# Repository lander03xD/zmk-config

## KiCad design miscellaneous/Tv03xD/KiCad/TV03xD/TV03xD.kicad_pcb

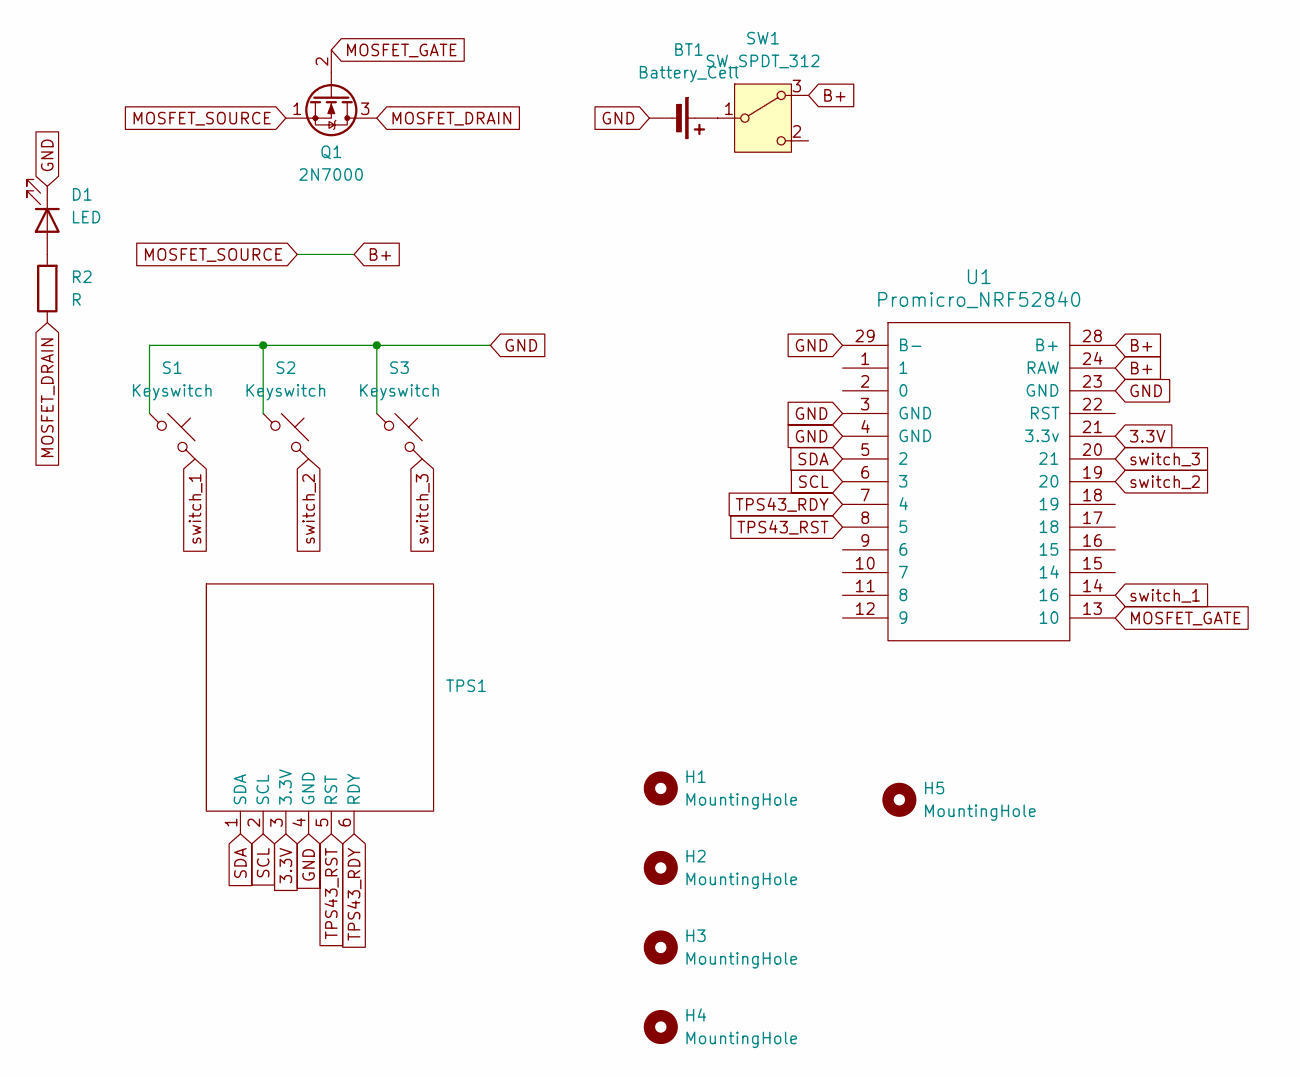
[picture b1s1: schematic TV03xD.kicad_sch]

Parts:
BT1: Battery_Cell; Battery pins
D1: LED; LED_D5.0mm
H1, H2, H3, H4, H5: MountingHole; MountingHole_2.2mm_M2
Q1: 2N7000; TO-92_Inline
R2: R; R_Axial_DIN0207_L6.3mm_D2.5mm_P7.62mm_Horizontal
S1, S2, S3: Keyswitch; Hotswap_Choc_V1V2_1.00u_18.5_throughole
SW1: SW_SPDT_312; powerswitch_SK12D07VG
TPS1: Azoteq ProxSense TPS43
U1: Promicro_NRF52840; Promicro_nrf52840_unprinted

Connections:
3.3V: TPS1.3 (3.3V), U1.21 (3.3v)
B+: Q1.1 (S), SW1.3 (A), U1.24 (RAW), U1.28 (B+)
GND: BT1.2 (-), D1.1 (K), S1.1, S2.1, S3.1, TPS1.4 (GND), U1.3 (GND), U1.4 (GND), U1.23 (GND), U1.29 (B-)
MOSFET_DRAIN: Q1.3 (D), R2.1
MOSFET_GATE: Q1.2 (G), U1.13 (10)
unnamed: BT1.1 (+), SW1.1 (B)
unnamed: D1.2 (A), R2.2
SCL: TPS1.2 (SCL), U1.6 (3)
SDA: TPS1.1 (SDA), U1.5 (2)
TPS43_RDY: TPS1.6 (RDY), U1.7 (4)
TPS43_RST: TPS1.5 (RST), U1.8 (5)
switch_1: S1.2, U1.14 (16)
switch_2: S2.2, U1.19 (20)
switch_3: S3.2, U1.20 (21)

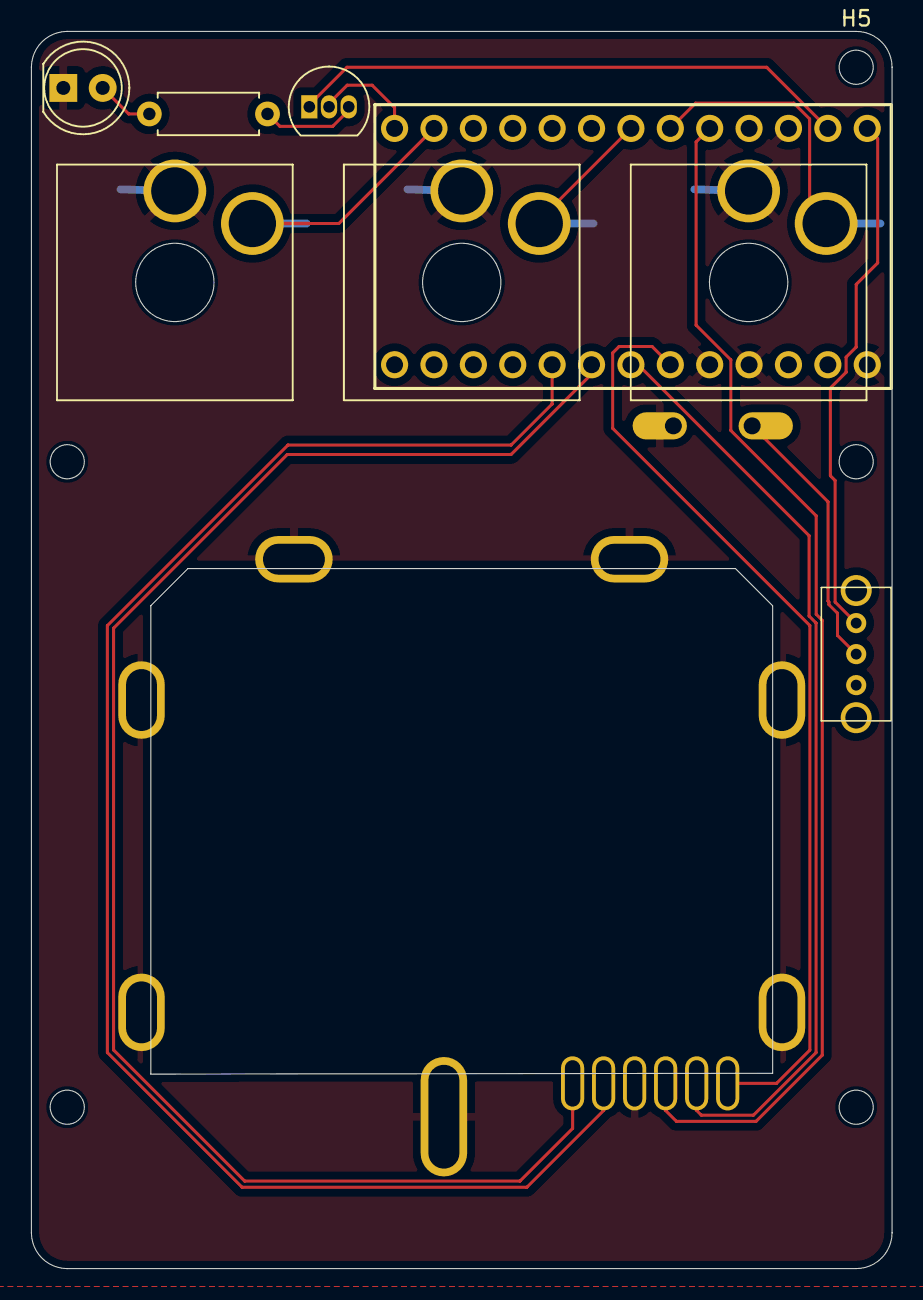
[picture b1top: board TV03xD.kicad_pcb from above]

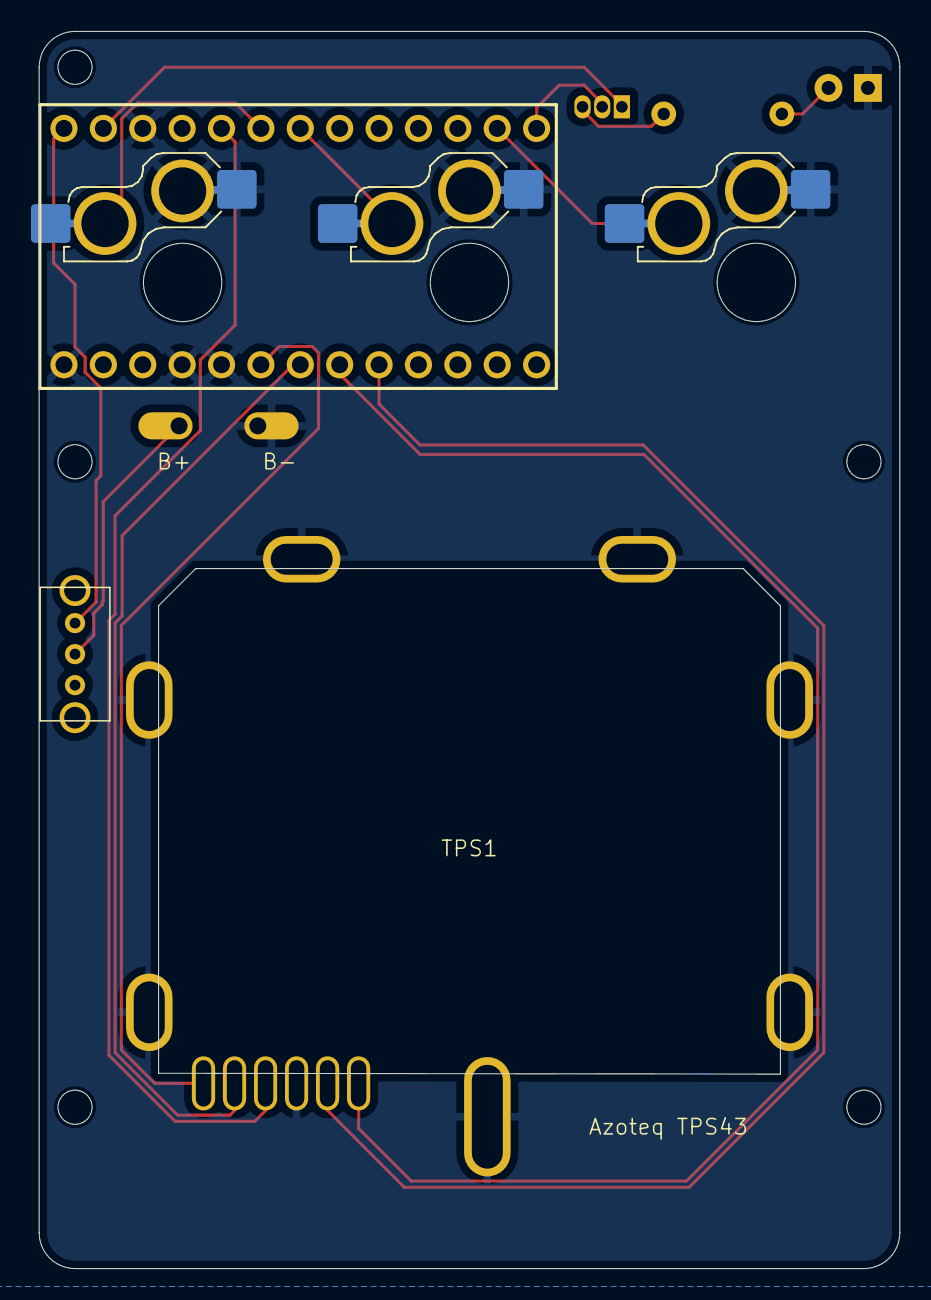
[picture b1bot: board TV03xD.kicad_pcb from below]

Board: 2 copper layers, 55.5 x 79.8 mm, 15 parts (2 on the bottom side), 14 nets.

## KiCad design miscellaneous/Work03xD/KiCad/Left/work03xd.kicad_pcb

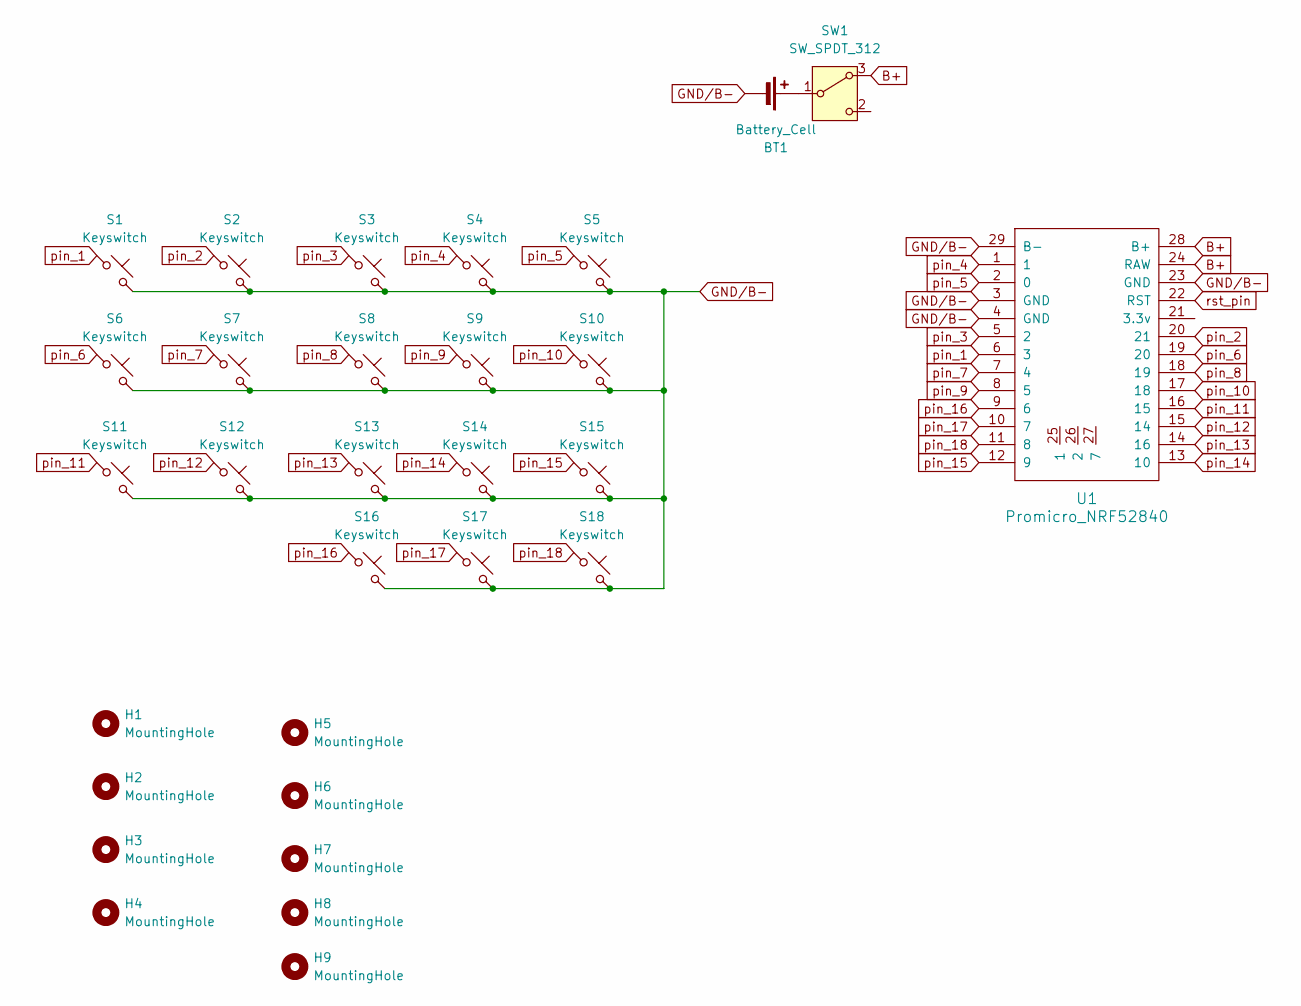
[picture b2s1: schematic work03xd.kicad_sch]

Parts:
BT1: Battery_Cell; Battery pins
H1, H2, H3, H4, H5, H6, H7, H8, H9: MountingHole; MountingHole_2.2mm_M2
S1, S2, S3, S4, S5, S6, S7, S8, S9, S10, S11, S12, S13, S14, S15, S16, S17, S18: Keyswitch; Hotswap_Choc_V1V2_1.00u_18.5_throughole
SW1: SW_SPDT_312; powerswitch_SK12D07VG
U1: Promicro_NRF52840; Promicro_nrf52840_unprinted

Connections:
B+: SW1.3 (A), U1.24 (RAW), U1.28 (B+)
GND/B-: BT1.2 (-), S1.2, S2.2, S3.2, S4.2, S5.2, S6.2, S7.2, S8.2, S9.2, S10.2, S11.2, S12.2, S13.2, S14.2, S15.2, S16.2, S17.2, S18.2, U1.3 (GND), U1.4 (GND), U1.23 (GND), U1.29 (B-)
unnamed: BT1.1 (+), SW1.1 (B)
pin_1: S1.1, U1.6 (3)
pin_2: S2.1, U1.20 (21)
pin_3: S3.1, U1.5 (2)
pin_4: S4.1, U1.1
pin_5: S5.1, U1.2 (0)
pin_6: S6.1, U1.19 (20)
pin_7: S7.1, U1.7 (4)
pin_8: S8.1, U1.18 (19)
pin_9: S9.1, U1.8 (5)
pin_10: S10.1, U1.17 (18)
pin_11: S11.1, U1.16 (15)
pin_12: S12.1, U1.15 (14)
pin_13: S13.1, U1.14 (16)
pin_14: S14.1, U1.13 (10)
pin_15: S15.1, U1.12 (9)
pin_16: S16.1, U1.9 (6)
pin_17: S17.1, U1.10 (7)
pin_18: S18.1, U1.11 (8)
rst_pin: U1.22 (RST)

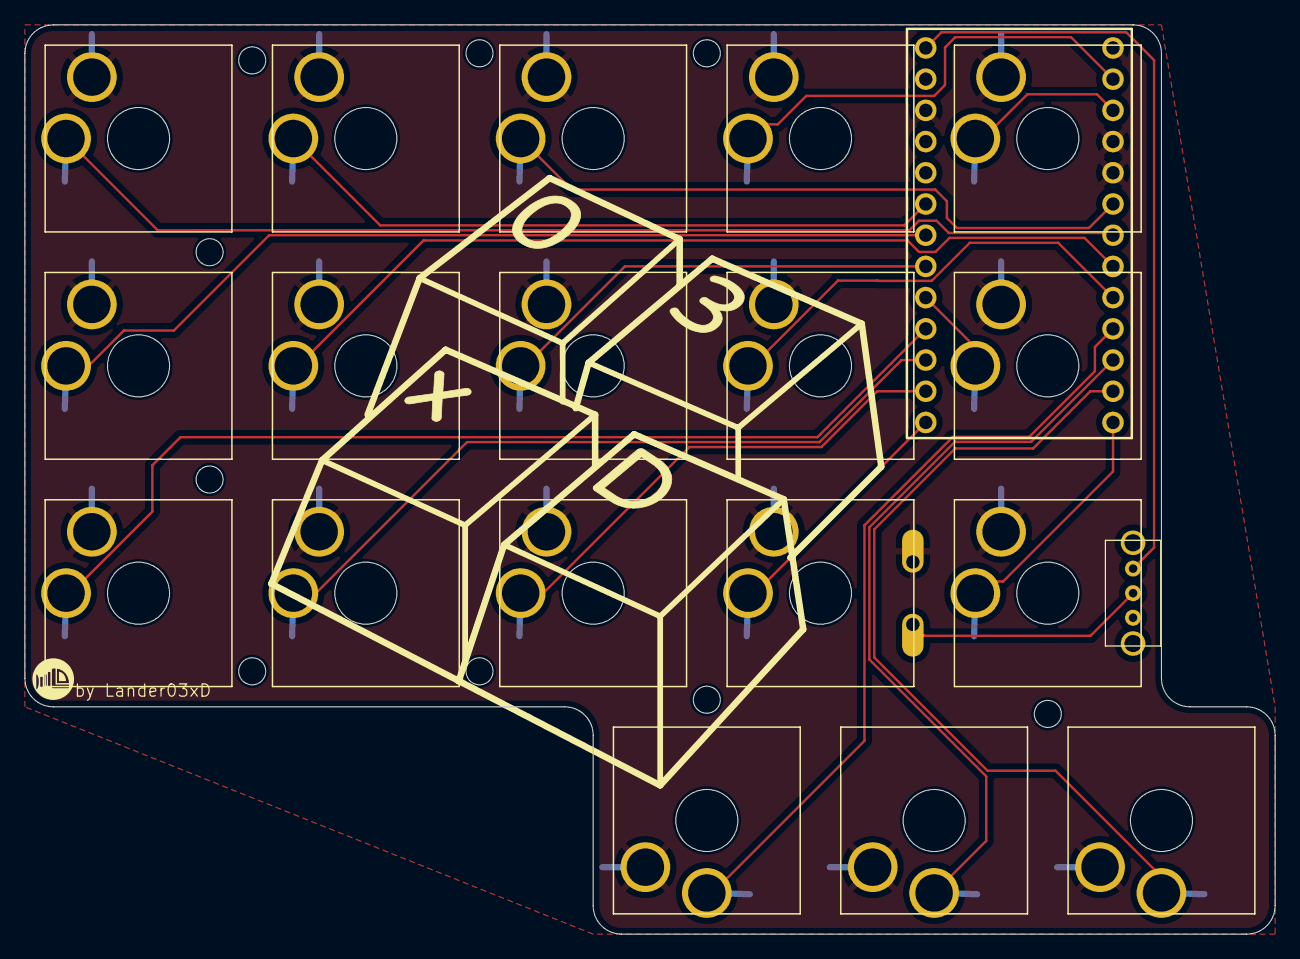
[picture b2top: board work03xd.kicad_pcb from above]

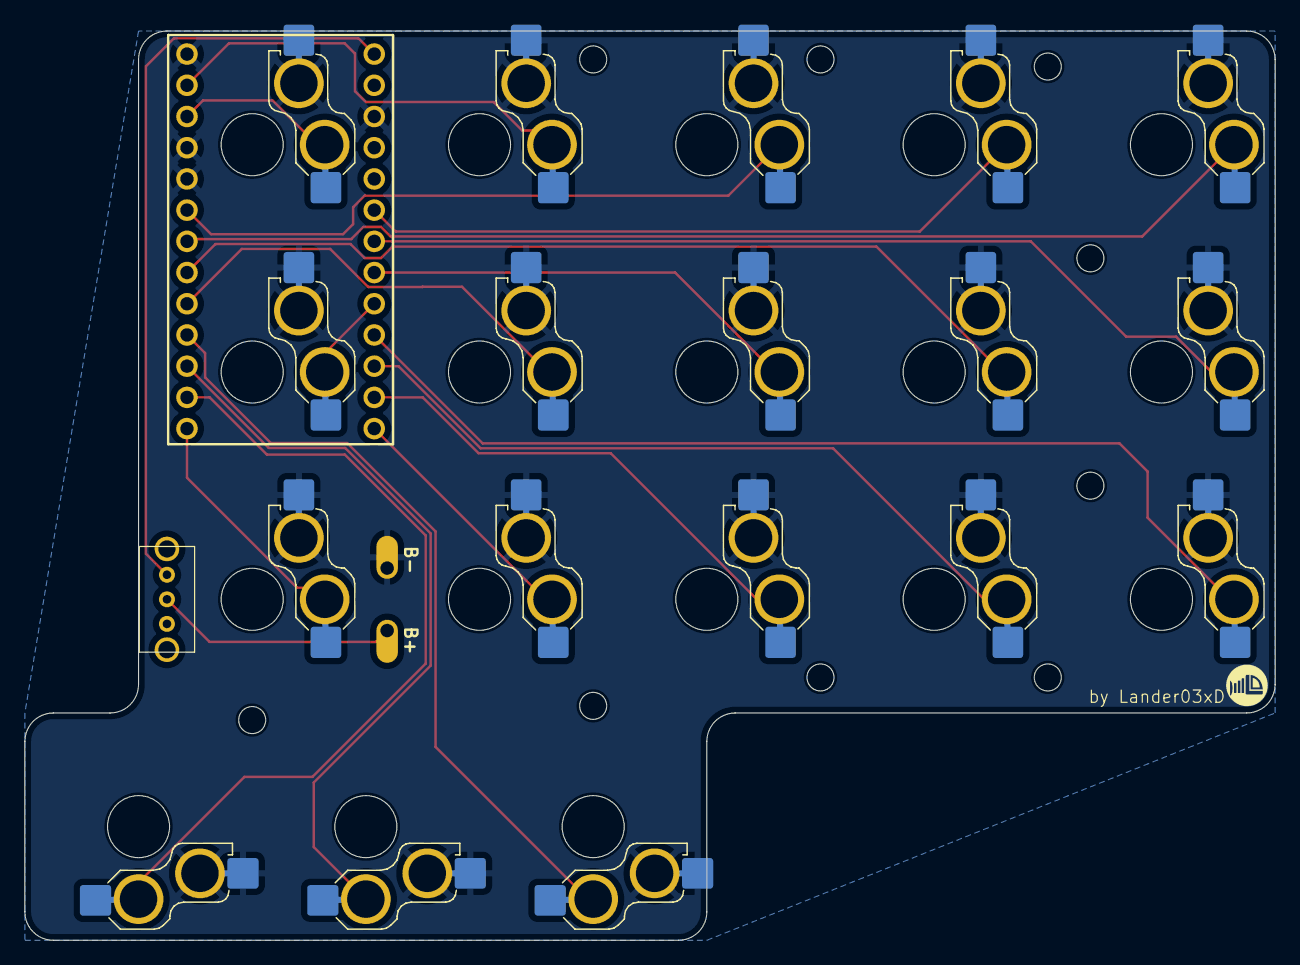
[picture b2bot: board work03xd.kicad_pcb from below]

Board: 2 copper layers, 101.8 x 74.0 mm, 30 parts (2 on the bottom side), 21 nets.

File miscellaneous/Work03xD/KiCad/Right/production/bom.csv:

Designator,Footprint,Quantity,Value,LCSC Part #
BT1,Battery pins,1,Battery_Cell,
"S1, S10, S11, S12, S13, S14, S15, S16, S17, S18, S2, S3, S4, S5, S6, S7, S8, S9",Hotswap_Choc_V1V2_1.00u_18.5_throughole,18,Keyswitch,
SW1,powerswitch_SK12D07VG,1,SW_SPDT_312,
U1,Promicro_nrf52840_unprinted,1,Promicro_NRF52840,

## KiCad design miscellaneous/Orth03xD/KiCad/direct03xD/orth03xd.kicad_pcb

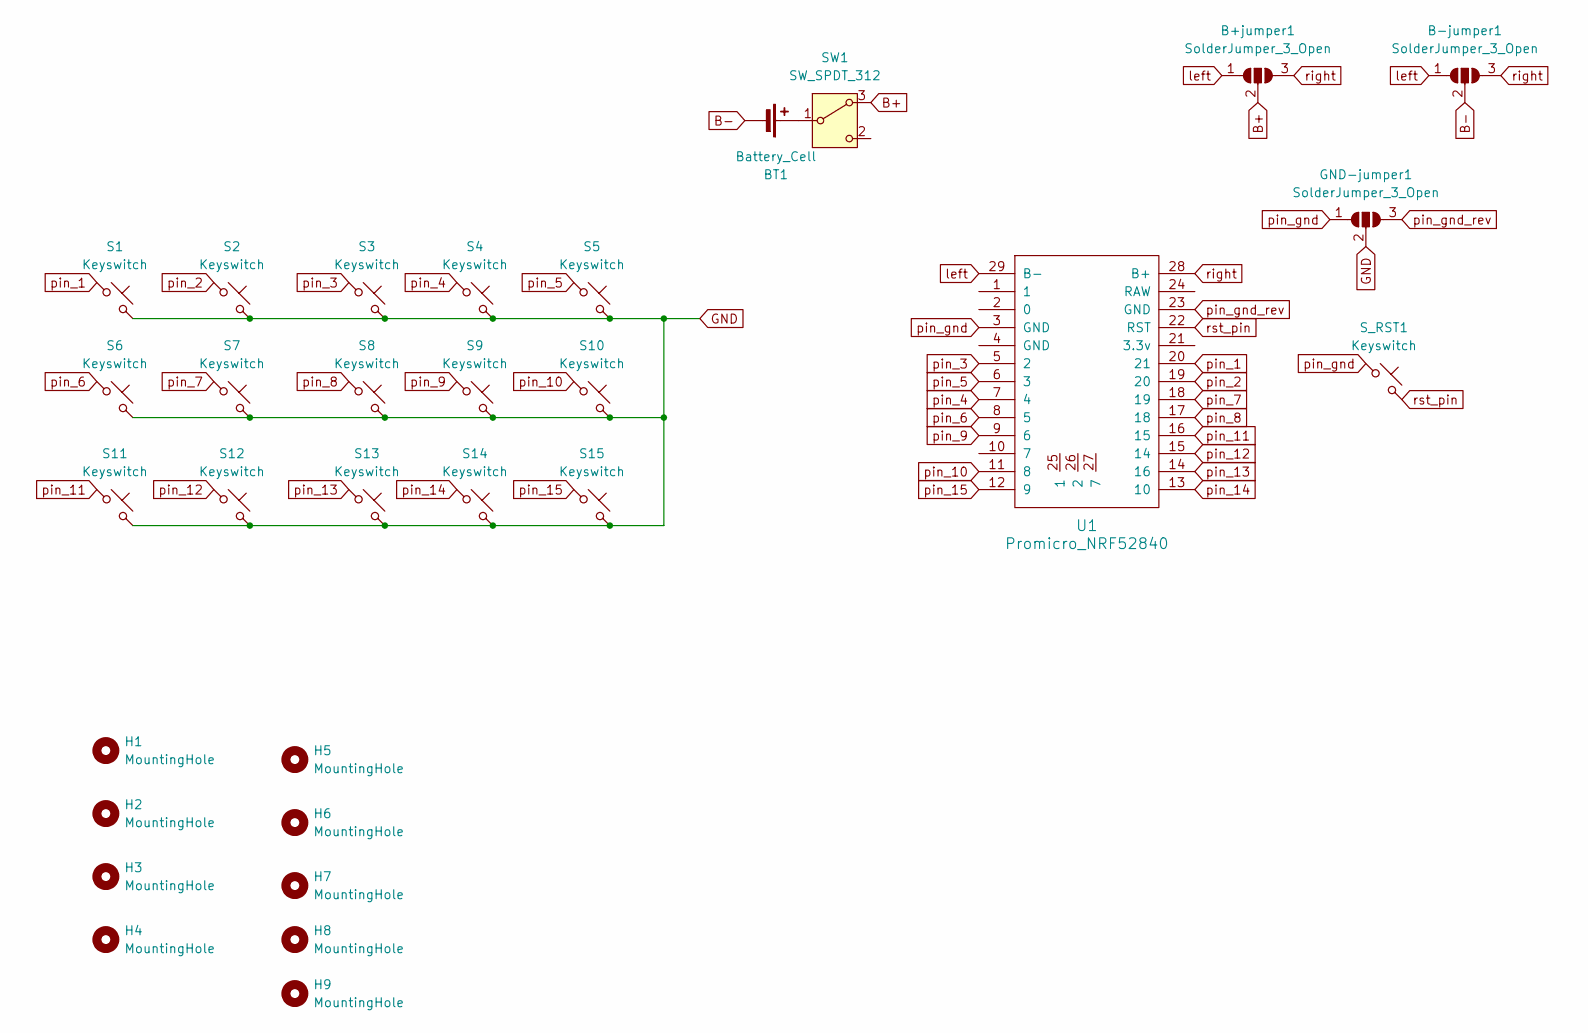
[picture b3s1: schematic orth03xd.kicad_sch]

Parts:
B+jumper1: SolderJumper_3_Open; jumper
B-jumper1: SolderJumper_3_Open; jumper
BT1: Battery_Cell; Battery pins
GND-jumper1: SolderJumper_3_Open; jumper
H1, H2, H3, H4, H5, H6, H7, H8, H9: MountingHole; MountingHole_2.2mm_M2
S1, S2, S3, S4, S5, S6, S7, S8, S9, S10, S11, S12, S13, S14, S15: Keyswitch; Hotswap_MX_1.00u_reversible_18.5mm
SW1: SW_SPDT_312; powerswitch_SK12D07VG
S_RST1: Keyswitch; KAILH_4.3mm_6.2x6.2_switch
U1: Promicro_NRF52840; Promicro_nrf52840_unprinted

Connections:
B+: B+jumper1.2 (C), SW1.3 (A)
B-: B-jumper1.2 (C), BT1.2 (-)
GND: GND-jumper1.2 (C), S1.2, S2.2, S3.2, S4.2, S5.2, S6.2, S7.2, S8.2, S9.2, S10.2, S11.2, S12.2, S13.2, S14.2, S15.2
unnamed: BT1.1 (+), SW1.1 (B)
left: B+jumper1.1 (A), B-jumper1.1 (A), U1.29 (B-)
pin_1: S1.1, U1.20 (21)
pin_2: S2.1, U1.19 (20)
pin_3: S3.1, U1.5 (2)
pin_4: S4.1, U1.7 (4)
pin_5: S5.1, U1.6 (3)
pin_6: S6.1, U1.8 (5)
pin_7: S7.1, U1.18 (19)
pin_8: S8.1, U1.17 (18)
pin_9: S9.1, U1.9 (6)
pin_10: S10.1, U1.11 (8)
pin_11: S11.1, U1.16 (15)
pin_12: S12.1, U1.15 (14)
pin_13: S13.1, U1.14 (16)
pin_14: S14.1, U1.13 (10)
pin_15: S15.1, U1.12 (9)
pin_gnd: GND-jumper1.1 (A), S_RST1.1, U1.3 (GND)
pin_gnd_rev: GND-jumper1.3 (B), U1.23 (GND)
right: B+jumper1.3 (B), B-jumper1.3 (B), U1.28 (B+)
rst_pin: S_RST1.2, U1.22 (RST)

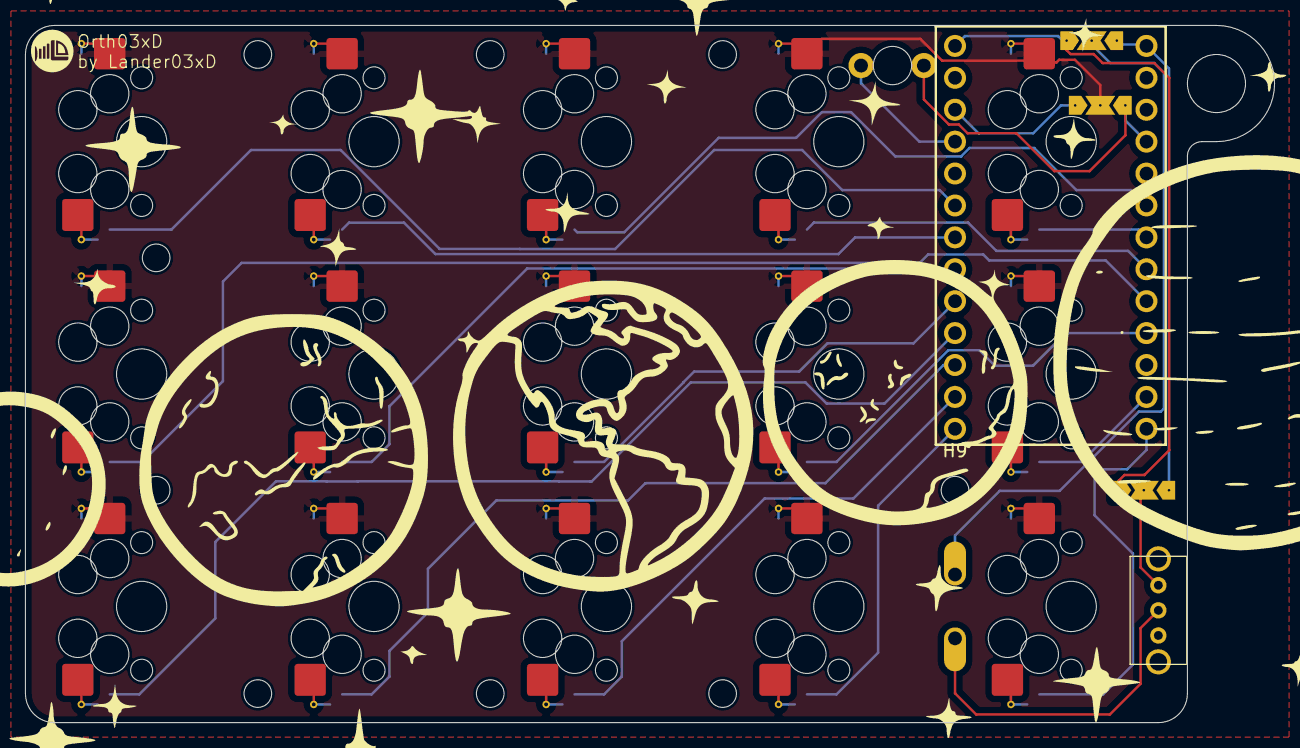
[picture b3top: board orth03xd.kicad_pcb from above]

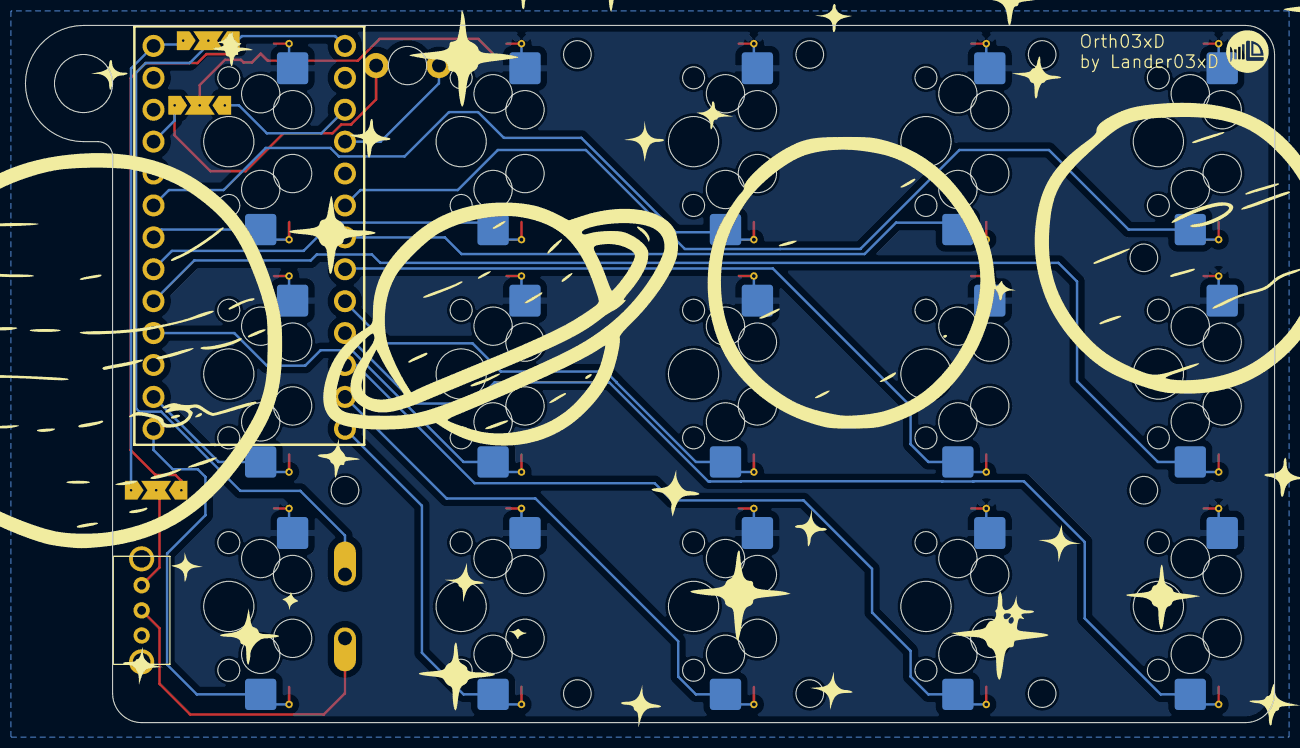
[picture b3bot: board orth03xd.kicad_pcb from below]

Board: 2 copper layers, 99.4 x 55.5 mm, 31 parts (4 on the bottom side), 24 nets.

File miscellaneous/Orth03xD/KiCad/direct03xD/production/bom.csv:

Designator,Footprint,Quantity,Value,LCSC Part #
BT1,Battery pins,1,Battery_Cell,
"S1, S10, S11, S12, S13, S14, S15, S2, S3, S4, S5, S6, S7, S8, S9",Hotswap_MX_1.00u_reversible_18.5mm,15,Keyswitch,
SW1,powerswitch_SK12D07VG,1,SW_SPDT_312,
S_RST1,KAILH_4.3mm_6.2x6.2_switch,1,Keyswitch,
U1,Promicro_nrf52840_unprinted,1,Promicro_NRF52840,

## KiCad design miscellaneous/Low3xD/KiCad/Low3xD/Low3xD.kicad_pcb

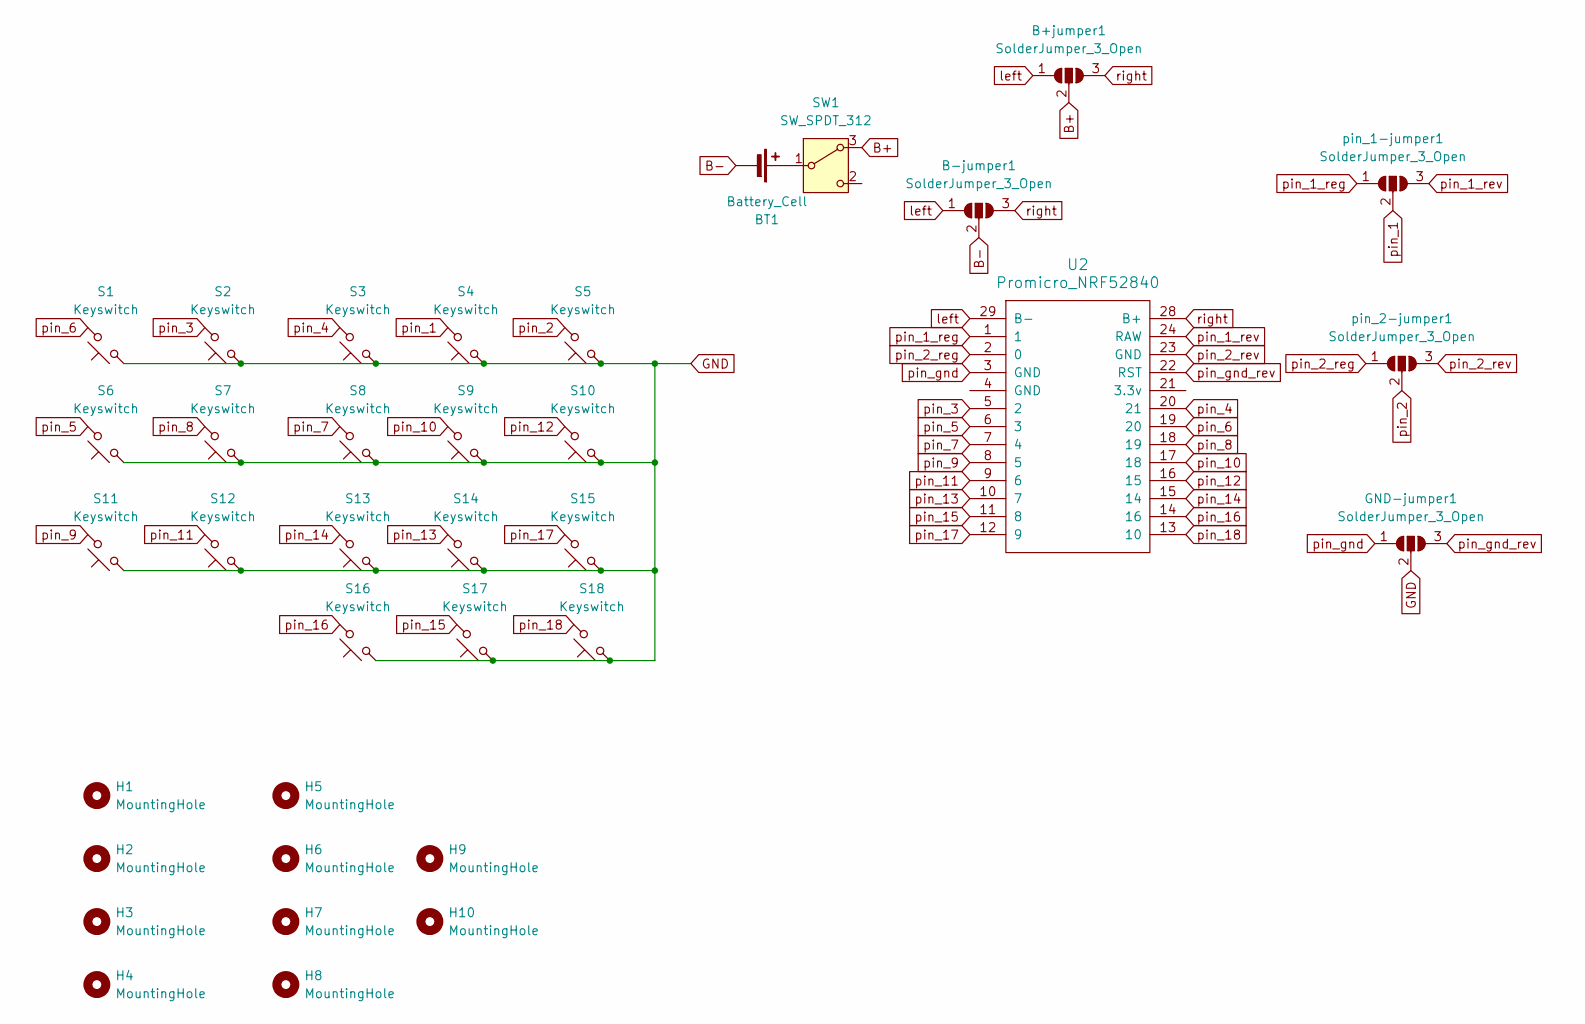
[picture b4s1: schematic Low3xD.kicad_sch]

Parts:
B+jumper1: SolderJumper_3_Open; jumper
B-jumper1: SolderJumper_3_Open; jumper
BT1: Battery_Cell; Battery pins
GND-jumper1: SolderJumper_3_Open; jumper
H1, H2, H3, H4, H5, H6, H7, H8, H9, H10: MountingHole; MountingHole_2.2mm_M2
S1, S2, S3, S4, S5, S6, S7, S8, S9, S10, S11, S12, S13, S14, S15, S16, S17, S18: Keyswitch; Hotswap_Choc_V1V2_rev_1.00u
SW1: SW_SPDT_312; SS-01B 1.5mm
U2: Promicro_NRF52840; Promicro_nrf52840_unprinted
pin_1-jumper1, pin_2-jumper1: SolderJumper_3_Open; jumper

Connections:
B+: B+jumper1.2 (C), SW1.3 (A)
B-: B-jumper1.2 (C), BT1.2 (-)
GND: GND-jumper1.2 (C), S1.1, S2.1, S3.1, S4.1, S5.1, S6.1, S7.1, S8.1, S9.1, S10.1, S11.1, S12.1, S13.1, S14.1, S15.1, S16.1, S17.1, S18.1
unnamed: BT1.1 (+), SW1.1 (B)
left: B+jumper1.1 (A), B-jumper1.1 (A), U2.29 (B-)
pin_1: S4.2, pin_1-jumper1.2 (C)
pin_1_reg: U2.1, pin_1-jumper1.1 (A)
pin_1_rev: U2.24 (RAW), pin_1-jumper1.3 (B)
pin_2: S5.2, pin_2-jumper1.2 (C)
pin_2_reg: U2.2 (0), pin_2-jumper1.1 (A)
pin_2_rev: U2.23 (GND), pin_2-jumper1.3 (B)
pin_3: S2.2, U2.5 (2)
pin_4: S3.2, U2.20 (21)
pin_5: S6.2, U2.6 (3)
pin_6: S1.2, U2.19 (20)
pin_7: S8.2, U2.7 (4)
pin_8: S7.2, U2.18 (19)
pin_9: S11.2, U2.8 (5)
pin_10: S9.2, U2.17 (18)
pin_11: S12.2, U2.9 (6)
pin_12: S10.2, U2.16 (15)
pin_13: S14.2, U2.10 (7)
pin_14: S13.2, U2.15 (14)
pin_15: S17.2, U2.11 (8)
pin_16: S16.2, U2.14 (16)
pin_17: S15.2, U2.12 (9)
pin_18: S18.2, U2.13 (10)
pin_gnd: GND-jumper1.1 (A), U2.3 (GND)
pin_gnd_rev: GND-jumper1.3 (B), U2.22 (RST)
right: B+jumper1.3 (B), B-jumper1.3 (B), U2.28 (B+)

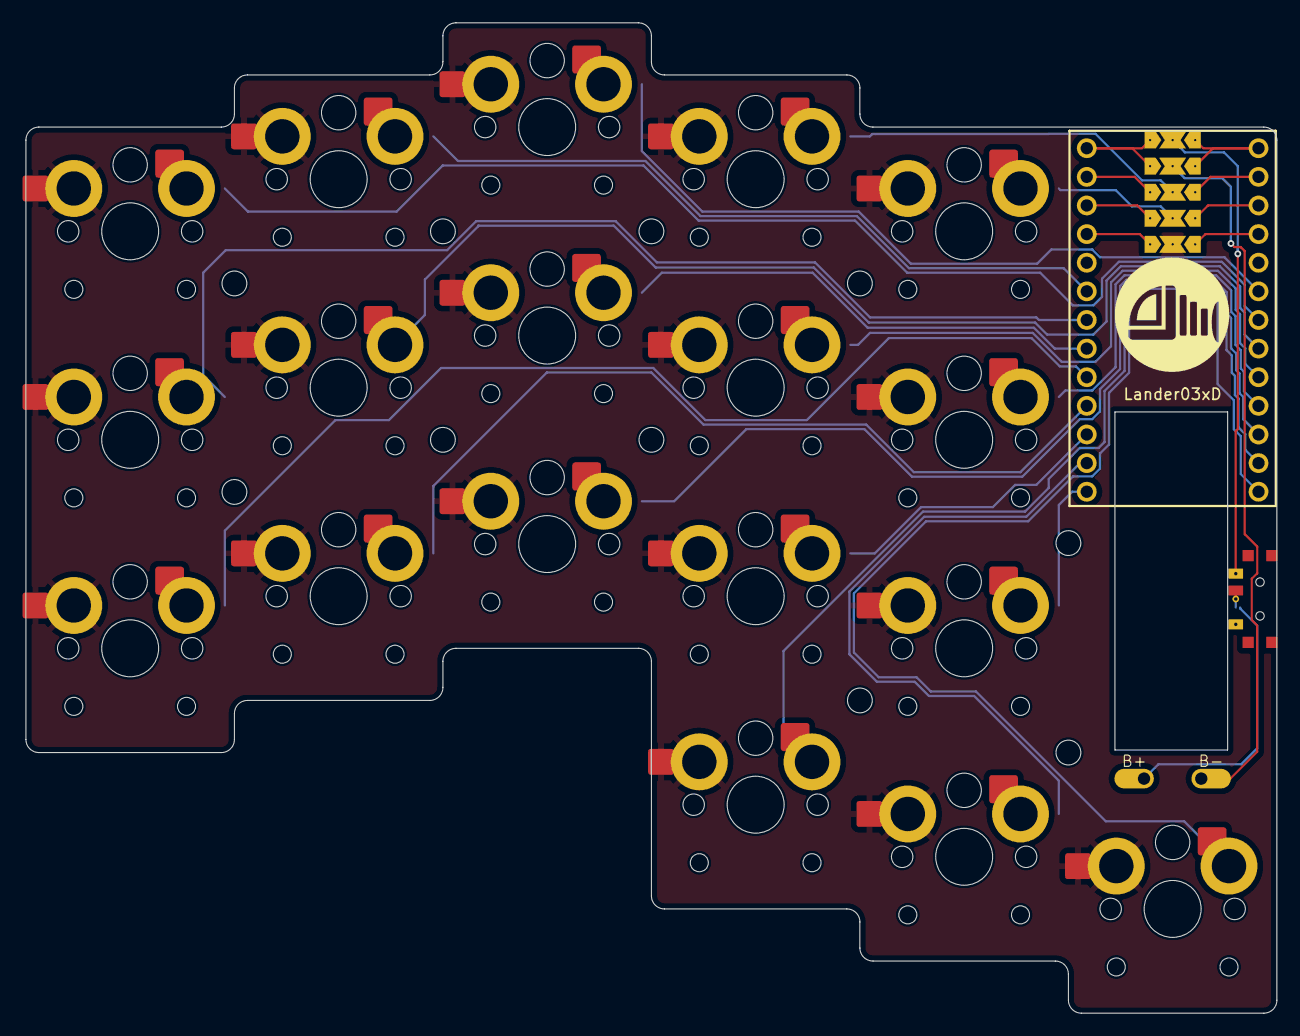
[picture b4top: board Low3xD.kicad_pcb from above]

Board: 2 copper layers, 111.0 x 87.9 mm, 36 parts (0 on the bottom side), 30 nets.

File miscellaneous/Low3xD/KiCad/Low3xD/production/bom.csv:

Designator,Footprint,Quantity,Value,LCSC Part #
BT1,Battery pins,1,Battery_Cell,
"S1, S10, S11, S12, S13, S14, S15, S16, S17, S18, S2, S3, S4, S5, S6, S7, S8, S9",Hotswap_Choc_V1V2_rev_1.00u,18,Keyswitch,
SW1,SS-01B 1.5mm,1,SW_SPDT_312,
U2,Promicro_nrf52840_unprinted,1,Promicro_NRF52840,

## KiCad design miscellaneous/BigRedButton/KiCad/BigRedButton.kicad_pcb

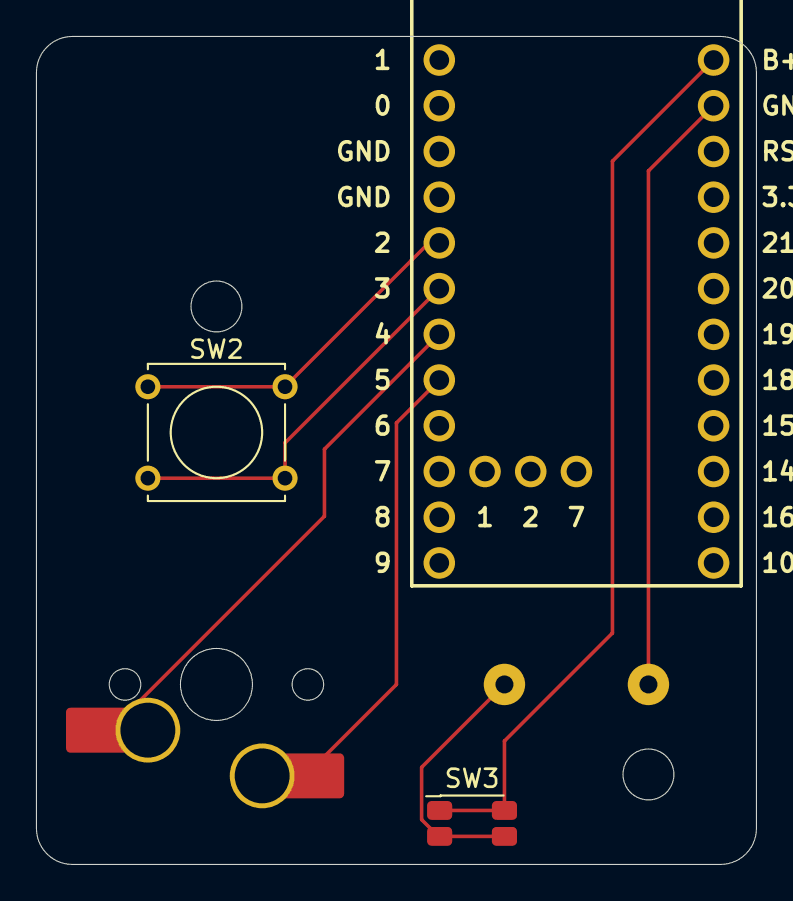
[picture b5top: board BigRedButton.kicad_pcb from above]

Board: 2 copper layers, 40.0 x 46.0 mm, 6 parts (0 on the bottom side), 7 nets.

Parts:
SW1: Switch; MX_Hotswap_1.00u
SW2: Switch; SW_Tactile_Straight_KSL0Axx1LFTR
SW3: Switch; SW_SPST_EVQP7A
TP1, TP2: TestPoint; TestPoint_Carvera
U1: Nice_Nano_V2

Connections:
BT_1: SW2.1, U1.5 (2)
BT_2: SW2.2, U1.6 (3)
unnamed: SW3.2, TP2.1
unnamed: TP1.1, U1.23 (GND)
unnamed: SW3.1, U1.24 (B+)
sink: SW1.2, U1.8 (5)
src: SW1.1, U1.7 (4)

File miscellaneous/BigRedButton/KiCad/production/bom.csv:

Designator,Footprint,Quantity,Value,LCSC Part #
SW1,MX_Hotswap_1.00u,1,Switch,
SW2,SW_Tactile_Straight_KSL0Axx1LFTR,1,Switch,
SW3,SW_SPST_EVQP7A,1,Switch,
"TP1, TP2",TestPoint_Carvera,2,TestPoint,
U1,Nice_Nano_V2,1,Nice_Nano_V2,

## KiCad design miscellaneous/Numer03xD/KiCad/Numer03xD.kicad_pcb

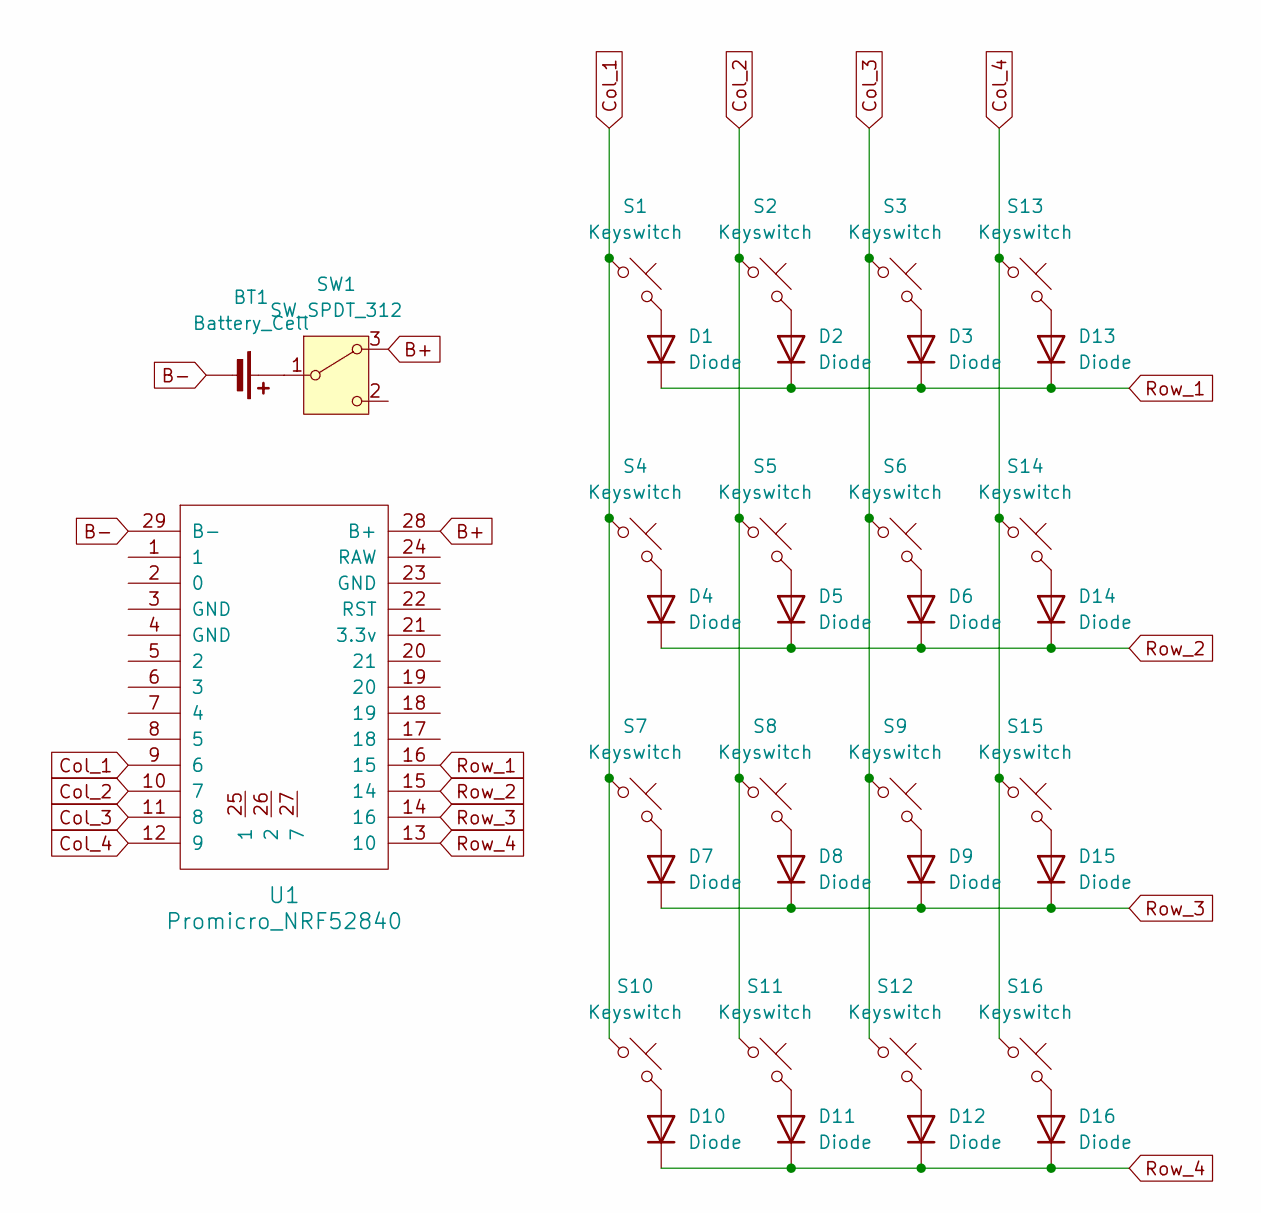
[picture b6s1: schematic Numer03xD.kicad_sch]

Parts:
BT1: Battery_Cell; SbM-9202_14250_battery_holder
D1, D2, D3, D4, D5, D6, D7, D8, D9, D10, D11, D12, D13, D14, D15, D16: Diode; Diode_SOD-123
S1, S2, S3, S4, S5, S6, S7, S8, S9, S10, S11, S12, S13, S14, S15, S16: Keyswitch; MX_Hotswap_1.00u
SW1: SW_SPDT_312; SW_Vertical_Slide_5mm
U1: Promicro_NRF52840; Promicro_nrf52840

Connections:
B+: SW1.3 (A), U1.28 (B+)
B-: BT1.2 (-), U1.29 (B-)
Col_1: S1.1, S4.1, S7.1, S10.1, U1.9 (6)
Col_2: S2.1, S5.1, S8.1, S11.1, U1.10 (7)
Col_3: S3.1, S6.1, S9.1, S12.1, U1.11 (8)
Col_4: S13.1, S14.1, S15.1, S16.1, U1.12 (9)
unnamed: BT1.1 (+), SW1.1 (B)
unnamed: D1.2 (A), S1.2
unnamed: D2.2 (A), S2.2
unnamed: D3.2 (A), S3.2
unnamed: D4.2 (A), S4.2
unnamed: D5.2 (A), S5.2
unnamed: D6.2 (A), S6.2
unnamed: D7.2 (A), S7.2
unnamed: D8.2 (A), S8.2
unnamed: D9.2 (A), S9.2
unnamed: D10.2 (A), S10.2
unnamed: D11.2 (A), S11.2
unnamed: D12.2 (A), S12.2
unnamed: D13.2 (A), S13.2
unnamed: D14.2 (A), S14.2
unnamed: D15.2 (A), S15.2
unnamed: D16.2 (A), S16.2
Row_1: D1.1 (K), D2.1 (K), D3.1 (K), D13.1 (K), U1.16 (15)
Row_2: D4.1 (K), D5.1 (K), D6.1 (K), D14.1 (K), U1.15 (14)
Row_3: D7.1 (K), D8.1 (K), D9.1 (K), D15.1 (K), U1.14 (16)
Row_4: D10.1 (K), D11.1 (K), D12.1 (K), D16.1 (K), U1.13 (10)
